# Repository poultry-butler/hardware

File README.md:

# Hardware

## Sensors
| Type | Name | URL | Price | Description |
|------|------|-----|-------|-------------|
| Hall | Hall Effect Sensor - US1881 | https://www.sparkfun.com/products/9312 | 0.95$ |  |
| Hall |  MICRONAS HAL510UA-E-1-A-2-00 | https://www.neuhold-elektronik.at/catshop/product_info.php?products_id=6079 | 1.95€/10 | |
| Hall | MICRONAS HAL510UA-C-1-B-1-00 | https://www.neuhold-elektronik.at/catshop/product_info.php?products_id=6385 | 1.95€/10 | |

## Actuators
| Type | URL | Price | Description |
|------|-----|-------|-------------|
| motor with gearbox and wheel | https://www.neuhold-elektronik.at/catshop/product_info.php?products_id=3365 | 10€ | |
| motor with gearbox | https://www.neuhold-elektronik.at/catshop/product_info.php?products_id=4237 | 15€ | |

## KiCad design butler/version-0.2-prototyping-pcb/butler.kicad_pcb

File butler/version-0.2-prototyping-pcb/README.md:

Prototyping Board
=================

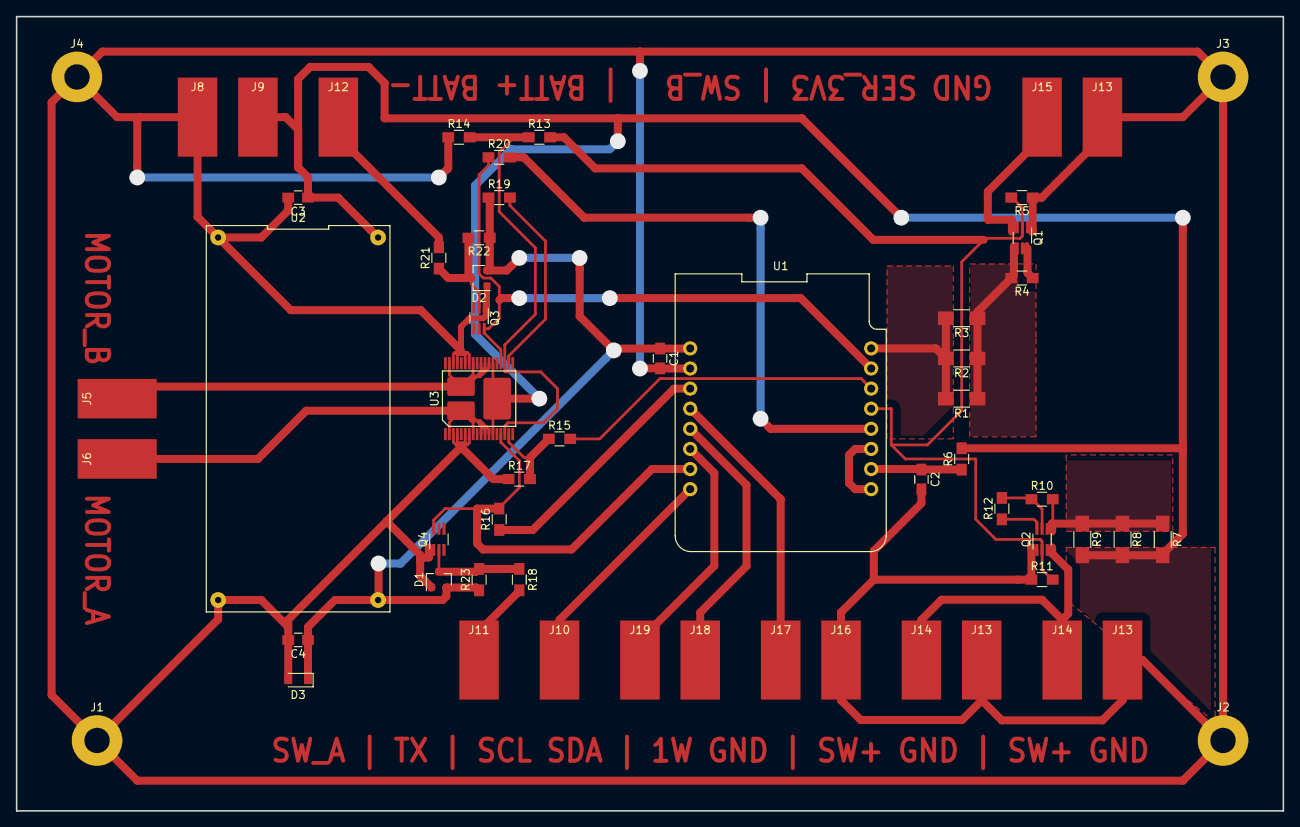
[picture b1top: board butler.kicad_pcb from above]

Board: 2 copper layers, 160.0 x 100.3 mm, 58 parts (0 on the bottom side), 32 nets.

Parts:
C1, C2, C3, C4: 1µ; C_0805_HandSoldering
D1, D2: BAT54S; SOT-23
D3: BZX84J-B5V1; D_SOD-323_HandSoldering
J1, J2, J3, J4: CONN_01X01; MountingHole_3.2mm_M3_Pad
J5: MOT_B; SolderWirePad_single_SMD_5x10mm
J6: MOT_A; SolderWirePad_single_SMD_5x10mm
J8: BATT-; SolderWirePad_single_SMD_5x10mm
J9: BATT+; SolderWirePad_single_SMD_5x10mm
J10: TX; SolderWirePad_single_SMD_5x10mm
J11: SWITCH_A; SolderWirePad_single_SMD_5x10mm
J12: SWITCH_B; SolderWirePad_single_SMD_5x10mm
J13, J13#2, J13#3, J16: GND; SolderWirePad_single_SMD_5x10mm
J14, J14#2: SW_V+; SolderWirePad_single_SMD_5x10mm
J15: SER_3V3; SolderWirePad_single_SMD_5x10mm
J17: 1W; SolderWirePad_single_SMD_5x10mm
J18: SDA; SolderWirePad_single_SMD_5x10mm
J19: SCL; SolderWirePad_single_SMD_5x10mm
Q1, Q2, Q3, Q4: P/N_MOS; SOT-363_SC-70-6_Handsoldering
R1, R2, R3: 33; R_1206_HandSoldering
R4, R5, R10, R11, R12, R22, R23: 100k; R_0805_HandSoldering
R6: 220k; R_0805_HandSoldering
R7, R8, R9: 100; R_1206_HandSoldering
R13, R15, R18, R21: 1k; R_0805_HandSoldering
R14, R16, R17, R19, R20: 10k; R_0805_HandSoldering
U1: WeMos_mini; wemos-d1-mini-with-pin-header-and-connector
U2: N9505; n9595
U3: VHN5180A-E; PowerSOIC-36

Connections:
/3V3: R1.2, R2.2, R3.2, U1.16
/BATT+: C3.1, J9.1, R6.2, R7.2, R8.2, R9.2, U2.1, U3.13, U3.24, U3.37
/EN_A: R16.1, U1.3
/EN_B: R20.2, U1.12
/EN_DIAG_B: R13.1, R14.2, U3.16, U3.21
/EN_DRIVER: Q1.2, Q2.2, R5.2, R11.2, R13.2, U1.13
/MOT_A: J6.1, U3.2, U3.8, U3.10, U3.11, U3.12, U3.38
/MOT_B: J5.1, U3.25, U3.26, U3.27, U3.29, U3.35, U3.39
/MOT_PWM: R15.2, U1.14
/OW: J17.1, U1.4
/SCL: J19.1, U1.6
/SDA: J18.1, U1.5
/SER_3V3: J15.1, Q1.3
/SWITCH_A: J11.1, R18.2
/SWITCH_B: J12.1, R21.2
/SW_A: Q4.6, R16.2, U1.7, U3.15
/SW_B: Q3.6, R20.1, U1.15, U3.22
/SW_V+: J14.1, J14#2.1, Q2.3
/TX: J10.1, U1.8
/WAKEUP: U1.9, U1.11
GND: C1.2, C2.2, C3.2, C4.2, D1.1, D2.1, D3.2, J1.1, J2.1, J3.1, J4.1, J8.1, J13.1, J13#2.1, J13#3.1, J16.1, Q1.1, Q2.1, Q3.1, Q4.1, R5.1, R11.1, R14.1, R17.1, U1.2, U2.2, U2.3, U3.3, U3.4, U3.6, U3.7, U3.30, U3.31, U3.33, U3.34
unnamed: C2.1, R6.1, U1.10
unnamed: D1.3, Q4.2, R18.1, R23.2
unnamed: D2.3, Q3.2, R21.1, R22.2
unnamed: Q1.4, R1.1, R2.1, R3.1, R4.2
unnamed: Q1.5, Q1.6, R4.1
unnamed: Q2.4, R7.1, R8.1, R9.1, R10.2
unnamed: Q2.5, R10.1, R12.2
unnamed: Q2.6, R12.1
unnamed: R15.1, R17.2, U3.17
unnamed: R19.2, U3.20
VCC: C1.1, C4.1, D1.2, D2.2, D3.1, R19.1, R22.1, R23.1, U1.1, U2.4

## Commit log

2017-01-25 added some datasheet
2017-01-26 added datasheet
2017-02-04 added Datasheet for WeMos mini and on Board LDO
2017-02-05 added some Battery Measurement and Info
2017-02-05 updates figure
2017-02-06 added one measurement
2017-02-08 added measurements
2017-02-13 initial schema
2017-02-13 added missing symlink
2017-02-14 refined schema
2017-02-26 added data sheets
2017-02-26 added libraries: connector, driver, diode, fet
2017-02-26 added several 3d models
2017-02-26 updated git ignore filter
2017-02-26 updated project libraries/3d packages
2017-02-26 added FreeCAD 3d shapes
2017-02-26 updated wemos d1 3d shape
2017-02-26 removed wemos submodule
2017-02-26 add unrouted board and project file update
2017-02-26 updated submodule
2017-02-27 updated libs and shapes
2017-02-27 begun a PCB draft
2017-02-27 refactored path of 3d shape
2017-02-27 renamed folder
2017-02-27 begun refactoring of wemos library placement
2017-02-27 routed first draft
2017-02-27 updated project file
2017-02-28 refactored library/shapes/footprint files placement
2017-02-28 removed submodule d1_mini_kicad
2017-02-28 cleanup
2017-02-28 added documentation
2017-02-28 fixed link
2017-02-28 updated documentation
2017-02-28 refactoring: renamed folder
2017-02-28 added submodule
2017-02-28 moved library to git-submodule
2017-02-28 updated library names after lib refactoring
2017-02-28 added version 0.1 which uses normally closed NPN proximity sensor
2017-02-28 updated step down n950 library shapes
2017-03-01 begun routing pcb version 0.2
2017-03-04 added fp-lib-table files
2017-03-05 added prototyping PCB
2017-03-05 minor change to satisfy DRC
